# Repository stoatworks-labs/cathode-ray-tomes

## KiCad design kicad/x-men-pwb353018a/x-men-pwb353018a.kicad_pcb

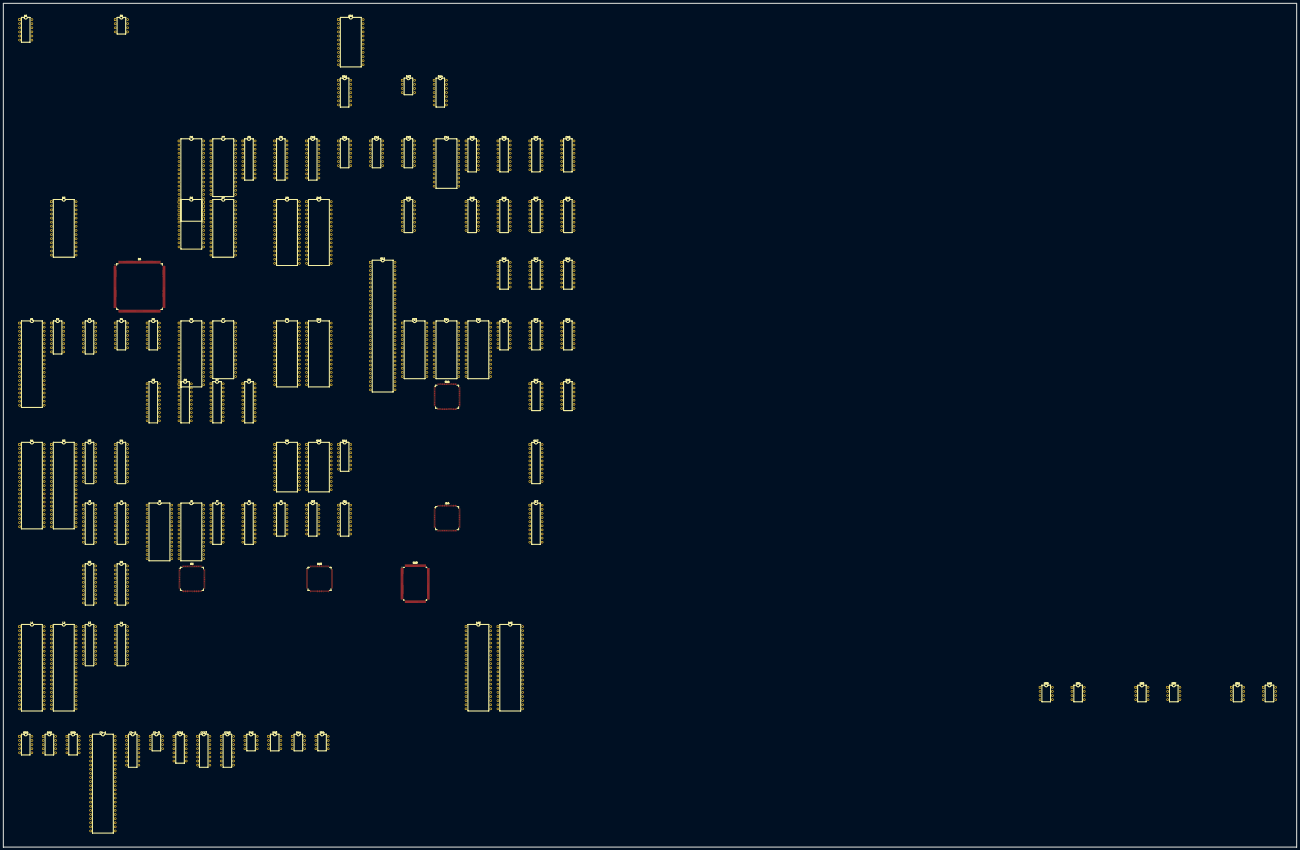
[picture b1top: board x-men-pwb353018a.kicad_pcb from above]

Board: 2 copper layers, 798.9 x 521.2 mm, 105 parts (0 on the bottom side), 659 nets, no tracks yet.

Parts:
A1: MB3722; DIP-12_W7.62mm
A4: LM358; DIP-8_W7.62mm
A11: 051550; DIP-24_W15.24mm
B11: 74LS07; DIP-14_W7.62mm
B13: ER5911; DIP-8_W7.62mm
B14: 74LS32; DIP-14_W7.62mm
BB9: 052535; DIP-10_W7.62mm
BG9: 052535; DIP-10_W7.62mm
BR9: 052535; DIP-10_W7.62mm
C4-1: 054321; DIP-48_W15.24mm
C4-2: AD1868R; DIP-16_W7.62mm
C4-3: MC33202; DIP-8_W7.62mm
C6: Z80CPU; DIP-40_W15.24mm
C7: MB8464A-10W-15W; DIP-28_W15.24mm
C8: PAL16L8; DIP-20_W7.62mm
C9, C10: 74LS273; DIP-20_W7.62mm
C11, C12: 74LS07; DIP-14_W7.62mm
C13: 74LS32; DIP-14_W7.62mm
C14: GAL22V10; DIP-24_W15.24mm
C15, C17, C18: 74LS257; DIP-16_W7.62mm
C16: 74LS367; DIP-16_W7.62mm
CC11: 74LS07; DIP-14_W7.62mm
CC13: 74LS174; DIP-16_W7.62mm
CC15: 74LS257; DIP-16_W7.62mm
D2: HM62256BLP; DIP-28_W15.24mm
D6: YM2151; DIP-24_W15.24mm
D7: MB8464A-10W-15W; DIP-28_W15.24mm
D9, D10: 27C020; DIP-32_W15.24mm
D13: 74LS161; DIP-16_W7.62mm
D15: 74LS139; DIP-16_W7.62mm
D16, D18: 74LS367; DIP-16_W7.62mm
D17: 74LS175; DIP-16_W7.62mm
E4: 054539; PQFP-160_28x28mm_P0.65mm
E12: 68000D; DIP-64_W15.24mm
E16: 74LS00; DIP-14_W7.62mm
E17: 74LS04; DIP-14_W7.62mm
E18: 74LS74; DIP-14_W7.62mm
F1: HN624116P; DIP-42_W15.24mm
F2: 74LS157; DIP-16_W7.62mm
F3: 74LS174; DIP-16_W7.62mm
F4, F17, F18: 74LS32; DIP-14_W7.62mm
F5: 74LS74; DIP-14_W7.62mm
F6, F9, F10: 27C020; DIP-32_W15.24mm
F7: MB8464A-10W-15W; DIP-28_W15.24mm
F13, F14, F15: MB8464A-80-10-15/L-LL; DIP-28_W15.24mm
F16: 74LS08; DIP-14_W7.62mm
G5, G6, G7, G8: 74LS245; DIP-20_W7.62mm
G14: 052109; TQFP-120_14x14mm_P0.4mm
G17: 74LS164; DIP-14_W7.62mm
G18: 74LS74; DIP-14_W7.62mm
H1, H2: 065A08; DIP-42_W15.24mm
H3, H4: 74LS374; DIP-20_W7.62mm
H9, H10: HM6116P-3; DIP-24_W15.24mm
H11: 74LS04; DIP-14_W7.62mm
H17: 74LS373; DIP-20_W7.62mm
J3, J4: 74LS374; DIP-20_W7.62mm
J5, J6: MB8464A-80-10-15/L-LL; DIP-28_W15.24mm
J7, J8: 74LS245; DIP-20_W7.62mm
J9, J10, J11: 74LS157; DIP-16_W7.62mm
J14: 051962; TQFP-120_14x14mm_P0.4mm
J17: 74LS373; DIP-20_W7.62mm
K3, K4: 74LS374; DIP-20_W7.62mm
K6: 053246; TQFP-120_14x14mm_P0.4mm
K10: 053247; TQFP-120_14x14mm_P0.4mm
K13: 053251; PQFP-100_14x20mm_P0.65mm
L1, L2, L15, L16: 065A08; DIP-42_W15.24mm
L3, L4: 74LS374; DIP-20_W7.62mm
S33, S34, S36, S37, S39, S40, S42, S43, S44, S54: KONAMI_005273; DIP-8_W7.62mm

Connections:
/+12V: A1.10, A11.19
/ACOL0: J14.46, K13.4
/ACOL1: J14.47, K13.5
/ACOL2: J14.48, K13.6
/ACOL3: J14.49, K13.7
/APAL0: J14.56, K13.8
/APAL1: J14.57, K13.9
/APAL2: J14.50, K13.10
/APAL3: J14.51, K13.20
/APAL4: J14.52, K13.21
/BCOL0: J14.30, K13.47
/BCOL1: J14.32, K13.48
/BCOL2: J14.33, K13.49
/BCOL3: J14.34, K13.50
/BPAL0: J14.35, K13.51
/BPAL1: J14.36, K13.52
/BPAL2: J14.37, K13.54
/BPAL3: J14.41, K13.55
/BPAL4: J14.42, K13.56
/BUSY: E4.11, F16.9
/COIN_CNT_1: A11.22, A11.23
/COIN_CNT_2: A11.20, A11.21
/CRAM~CS: C14.20, G7.19, G8.19, J9.1, J9.14, J10.1, J11.1
/CR~CS: D15.7, K10.9
/FCOL0: J14.59, K13.57
/FCOL1: J14.60, K13.58
/FCOL2: J14.62, K13.59
/FCOL3: J14.63, K13.60
/FPAL0: J14.64, K13.61
/FPAL1: J14.65, K13.62
/FPAL2: J14.66, K13.63
/FPAL3: J14.67, K13.64
/INTDMAEN: CC13.15, E18.10
/MAIN_A0: G6.3, G14.66, J14.88, K6.7, K10.7, K13.85
/MAIN_A1: C4-1.35, D7.10, D9.12, D10.12, E12.29, E17.1, F7.10, F9.12, F10.12, G6.4, G14.67, J11.2, J14.89, K6.6, K10.6, K13.84
/MAIN_A2: C4-1.34, D7.9, D9.11, D10.11, D15.2, E12.30, F7.9, F9.11, F10.11, G6.5, G14.68, J11.5, K13.83
/MAIN_A3: C4-1.33, D7.8, D9.10, D10.10, D15.3, E12.31, F7.8, F9.10, F10.10, G6.6, G14.69, J11.11, K13.82
/MAIN_A4: C4-1.32, D7.7, D9.9, D10.9, E12.32, F7.7, F9.9, F10.9, G6.7, G14.116, J11.14
/MAIN_A5: D7.6, D9.8, D10.8, D15.14, E12.33, F7.6, F9.8, F10.8, G6.8, G14.115, J10.2
/MAIN_A6: D7.5, D9.7, D10.7, D15.13, E12.34, F7.5, F9.7, F10.7, G6.9, G14.114, J10.5
/MAIN_A7: D7.4, D9.6, D10.6, E12.35, F7.4, F9.6, F10.6, G5.2, G14.113, J10.11
/MAIN_A8: D7.3, D9.5, D10.5, E12.36, F7.3, F9.5, F10.5, G5.3, G14.112, J10.14
/MAIN_A9: D7.25, D9.27, D10.27, E12.37, F7.25, F9.27, F10.27, G5.4, G14.111, J9.2
/MAIN_A10: D7.24, D9.26, D10.26, E12.38, F7.24, F9.26, F10.26, G5.5, G14.110, J9.5
/MAIN_A11: D7.21, D9.23, D10.23, E12.39, F7.21, F9.23, F10.23, G5.6, G14.109, J9.11
/MAIN_A12: D7.23, D9.25, D10.25, E12.40, F7.23, F9.25, F10.25, G6.2, G14.80
/MAIN_A13: C14.13, D7.2, D9.4, D10.4, E12.41, F7.2, F9.4, F10.4, G14.81
/MAIN_A14: C14.11, D9.28, D10.28, E12.42, F9.28, F10.28, G14.82
/MAIN_A15: C14.10, D9.29, D10.29, E12.43, F9.29, F10.29, G14.83
/MAIN_A16: C14.9, D9.3, D10.3, E12.44, F9.3, F10.3
/MAIN_A17: C14.8, D9.2, D10.2, E12.45, F9.2, F10.2
/MAIN_A18: C14.7, D9.30, D10.30, E12.46, F9.30, F10.30
/MAIN_A19: C13.13, C14.6, E12.47, E17.3
/MAIN_A20: C14.5, E12.48
/MAIN_A23: C14.4, E12.52, E16.13
/MAIN_D0: C4-1.44, CC13.3, CC15.4, D16.3, E12.5, F7.11, F9.13, F10.13, G7.2, G14.56, J7.2, J14.79, K10.30, K13.80
/MAIN_D1: C4-1.43, CC13.4, CC15.7, D16.5, E12.4, F7.12, F9.14, F10.14, G7.3, G14.57, J7.3, J14.80, K10.29, K13.79
/MAIN_D2: C4-1.42, CC13.6, CC15.9, D16.7, E12.3, F7.13, F9.15, F10.15, G7.4, G14.58, J7.4, J14.81, K10.28, K13.77
/MAIN_D3: C4-1.41, CC13.11, CC15.12, D16.9, E12.2, F7.15, F9.17, F10.17, G7.5, G14.59, J7.5, J14.82, K10.27, K13.76
/MAIN_D4: C4-1.40, C15.4, CC13.13, E12.1, F7.16, F9.18, F10.18, G7.6, G14.60, J7.6, J14.83, K10.26, K13.75
/MAIN_D5: C4-1.39, C15.7, CC13.14, E12.64, F7.17, F9.19, F10.19, G7.7, G14.62, J7.7, J14.84, K10.25, K13.74
/MAIN_D6: C4-1.38, C15.9, D16.11, E12.63, F7.18, F9.20, F10.20, G7.8, G14.63, J7.8, K10.24
/MAIN_D7: C4-1.37, C15.12, D16.13, E12.62, F7.19, F9.21, F10.21, G7.9, G14.64, J7.9, J14.86, K10.23
/MAIN_D8: C16.3, C18.4, D7.11, D9.13, D10.13, D17.4, E12.61, G8.2, J8.2, K10.22
/MAIN_D9: C16.5, C18.7, D7.12, D9.14, D10.14, D17.5, E12.60, G8.3, J8.3, K10.20
/MAIN_D10: C16.7, C18.9, D7.13, D9.15, D10.15, D17.12, E12.59, G8.4, J8.4, K10.19
/MAIN_D11: C16.9, C18.12, D7.15, D9.17, D10.17, D17.13, E12.58, G8.5, J8.5, K10.18
/MAIN_D12: C17.4, D7.16, D9.18, D10.18, E12.57, G8.6, J8.6, K10.17
/MAIN_D13: C17.7, D7.17, D9.19, D10.19, E12.56, G8.7, J8.7, K10.15
/MAIN_D14: C16.11, C17.9, D7.18, D9.20, D10.20, E12.55, G8.8, J8.8, K10.14
/MAIN_D15: C16.13, C17.12, D7.19, D9.21, D10.21, E12.54, G8.9, J8.9, K10.13
/MAIN~IRQ: F16.2, F17.2, G14.87
/MCLK: D13.14, E12.15
/MCO~WRH: F18.3, H10.21
/MCO~WRL: F18.6, H9.21
/MUTE: C12.1, D17.14
/M~RD: B14.9, C13.5, E17.8, G5.7, G7.1, G8.1, G14.85, J7.1, J8.1, J14.87
/OBJCLK6: C9.11, C10.11, E17.13, H11.11, J14.78, K6.12, K10.12
/OBJCLK12: H11.3, J14.95, K6.10, K10.10
/OBJDMA: F17.9, G5.19, G6.19, H11.1, K6.116
/OBJROMA0: H1.10, H2.10, K6.68, L1.10, L2.10
/OBJROMA1: H1.9, H2.9, K6.69, L1.9, L2.9
/OBJROMA2: H1.8, H2.8, K6.70, L1.8, L2.8
/OBJROMA3: H1.7, H2.7, K6.72, L1.7, L2.7
/OBJROMA4: H1.6, H2.6, K6.73, L1.6, L2.6
/OBJROMA5: H1.5, H2.5, K6.74, L1.5, L2.5
/OBJROMA6: H1.4, H2.4, K6.75, L1.4, L2.4
/OBJROMA7: H1.3, H2.3, K6.77, L1.3, L2.3
/OBJROMA8: H1.41, H2.41, K6.78, L1.41, L2.41
/OBJROMA9: H1.40, H2.40, K6.79, L1.40, L2.40
/OBJROMA10: H1.39, H2.39, K6.80, L1.39, L2.39
/OBJROMA11: H1.38, H2.38, K6.82, L1.38, L2.38
/OBJROMA12: H1.37, H2.37, K6.83, L1.37, L2.37
/OBJROMA13: H1.36, H2.36, K6.84, L1.36, L2.36
/OBJROMA14: H1.35, H2.35, K6.85, L1.35, L2.35
/OBJROMA15: H1.34, H2.34, K6.86, L1.34, L2.34
/OBJROMA16: H1.33, H2.33, K6.87, L1.33, L2.33
/OBJROMA17: H1.2, H2.2, K6.88, L1.2, L2.2
/OBJROMA18: H1.1, H2.1, K6.89, L1.1, L2.1
/OBJROMA19: H1.42, H2.42, K6.90, L1.42, L2.42
/OBJ~CS: C14.18, F16.13
/OBJ~REG: D15.11, F16.12, K6.2, K10.2
/OCHARA: D17.3, K6.9
/OCOL0: K10.32, K13.30
/OCOL1: K10.33, K13.31
/OCOL2: K10.34, K13.32
/OCOL3: K10.35, K13.33
/OCOL4: K10.36, K13.34
/OCOL5: K10.37, K13.35
/OCOL6: K10.38, K13.36
/OCOL7: K10.39, K13.37
/OCOL8: K10.40, K13.38
/OPRI0: K10.42, K13.23
/OPRI1: K10.43, K13.24
/OPRI2: K10.44, K13.25
/OPRI3: K10.45, K13.27
/OPRI4: K10.47, K13.29
/ORAM~WEH: F4.6, J5.27
/ORAM~WEL: F4.8, J6.27
/PAIR~CS: C4-1.36, D15.10
/PAS: E16.12, E17.10, F5.11
/PCM0: C4-1.1, E4.34
/PCM1: C4-1.2, E4.26
/PCM2: C4-1.3, E4.27
/PCU~CS: D15.9, K13.81
/R/~W: B14.2, B14.13, C14.2, E12.9, E17.9
/SCR_PQ: E18.3, F18.13, G14.89
/SCR~CLK: G14.65, G18.3, H11.6, J14.90
/SHD0: K10.48, K13.95
/SHD1: K10.49, K13.96
/SIC_CLK: C4-1.7, C4-2.4, E4.28
/SND_A0: C4-1.21, C6.30, C7.10, D6.4, E4.52, F6.12
/SND_A1: C4-1.22, C6.31, C7.9, E4.51, F6.11
/SND_A2: C6.32, C7.8, E4.49, F6.10
/SND_A3: C6.33, C7.7, E4.48, F6.9
/SND_A4: C6.34, C7.6, E4.47, F6.8
/SND_A5: C6.35, C7.5, E4.46, F6.7
/SND_A6: C6.36, C7.4, E4.45, F6.6
/SND_A7: C6.37, C7.3, E4.44, F6.5
/SND_A8: C6.38, C7.25, F6.27
/SND_A9: C6.39, C7.24, E4.42, F6.26
/SND_A10: C6.40, C7.21, C8.11, F6.23
/SND_A11: C6.1, C7.23, C8.9, F6.25
/SND_A12: C6.2, C7.2, C8.8, F6.4
/SND_A13: C6.3, C8.7, F6.28
/SND_A14: C6.4, C8.6
/SND_A15: C6.5, C8.5, F2.1
/SND_D0: C4-1.12, C6.14, C7.11, D6.10, E4.9, F3.3, F6.13
/SND_D1: C4-1.13, C6.15, C7.12, D6.12, E4.8, F3.4, F6.14
/SND_D2: C4-1.14, C6.12, C7.13, D6.13, E4.7, F3.6, F6.15
/SND_D3: C4-1.15, C6.8, C7.15, D6.14, E4.6, F3.11, F6.17
/SND_D4: C4-1.16, C6.7, C7.16, D6.15, E4.5, F3.13, F6.18
/SND_D5: C4-1.17, C6.9, C7.17, D6.16, E4.4, F3.14, F6.19
/SND_D6: C4-1.18, C6.10, C7.18, D6.17, E4.3, F6.20
/SND_D7: C4-1.19, C6.13, C7.19, D6.18, E4.2, F6.21
/SND~PAL8: C4-1.24, C8.12
/SYS~RES: G14.55, G18.5, J14.92
/S~CLK: C4-1.5, C6.6, D13.13
/S~INT: C4-1.8, C6.16
/S~IORQ: C4-1.29, C6.20
/S~RD: C4-1.25, C6.21, C7.22, C8.2, D6.6, E4.67
/S~RST: C4-1.4, C6.26, D6.3, E4.71, F3.1
/S~WAIT: C6.24, F16.8
/S~WR: C4-1.26, C6.22, C7.27, D6.5, E4.68
/VSYNC: H11.8, K6.119
/V~CHARA: D17.7, G14.97, J14.96
/XOBJROMD0: K3.3, L1.14
/XOBJROMD1: K3.4, L1.16
/XOBJROMD2: K3.7, L1.18
/XOBJROMD3: K3.8, L1.20
/XOBJROMD4: K3.13, L1.23
/XOBJROMD5: K3.14, L1.25
/XOBJROMD6: K3.17, L1.27
/XOBJROMD7: K3.18, L1.29
/XOBJROMD8: L1.15, L3.3
/XOBJROMD9: L1.17, L3.4
/XOBJROMD10: L1.19, L3.7
/XOBJROMD11: L1.21, L3.8
/XOBJROMD12: L1.24, L3.13
/XOBJROMD13: L1.26, L3.14
/XOBJROMD14: L1.28, L3.17
/XOBJROMD15: L1.30, L3.18
/XOBJROMD16: H1.14, H3.3
/XOBJROMD17: H1.16, H3.4
/XOBJROMD18: H1.18, H3.7
/XOBJROMD19: H1.20, H3.8
/XOBJROMD20: H1.23, H3.13
/XOBJROMD21: H1.25, H3.14
/XOBJROMD22: H1.27, H3.17
/XOBJROMD23: H1.29, H3.18
/XOBJROMD24: H1.15, J3.3
/XOBJROMD25: H1.17, J3.4
/XOBJROMD26: H1.19, J3.7
/XOBJROMD27: H1.21, J3.8
/XOBJROMD28: H1.24, J3.13
/XOBJROMD29: H1.26, J3.14
/XOBJROMD30: H1.28, J3.17
/XOBJROMD31: H1.30, J3.18
/YOBJROMD0: K4.3, L2.14
/YOBJROMD1: K4.4, L2.16
/YOBJROMD2: K4.7, L2.18
/YOBJROMD3: K4.8, L2.20
/YOBJROMD4: K4.13, L2.23
/YOBJROMD5: K4.14, L2.25
/YOBJROMD6: K4.17, L2.27
/YOBJROMD7: K4.18, L2.29
/YOBJROMD8: L2.15, L4.3
/YOBJROMD9: L2.17, L4.4
/YOBJROMD10: L2.19, L4.7
/YOBJROMD11: L2.21, L4.8
/YOBJROMD12: L2.24, L4.13
/YOBJROMD13: L2.26, L4.14
/YOBJROMD14: L2.28, L4.17
/YOBJROMD15: L2.30, L4.18
/YOBJROMD16: H2.14, H4.3
/YOBJROMD17: H2.16, H4.4
/YOBJROMD18: H2.18, H4.7
/YOBJROMD19: H2.20, H4.8
/YOBJROMD20: H2.23, H4.13
/YOBJROMD21: H2.25, H4.14
/YOBJROMD22: H2.27, H4.17
/YOBJROMD23: H2.29, H4.18
/YOBJROMD24: H2.15, J4.3
/YOBJROMD25: H2.17, J4.4
/YOBJROMD26: H2.19, J4.7
/YOBJROMD27: H2.21, J4.8
/YOBJROMD28: H2.24, J4.13
/YOBJROMD29: H2.26, J4.14
/YOBJROMD30: H2.28, J4.17
/YOBJROMD31: H2.30, J4.18
/colmix/COL0: J11.3, K13.19
/colmix/COL1: J11.6, K13.18
/colmix/COL2: J11.10, K13.17
/colmix/COL3: J11.13, K13.16
/colmix/COL4: J10.3, K13.14
/colmix/COL5: J10.6, K13.13
/colmix/COL6: J10.10, K13.12
/colmix/COL7: J10.13, K13.11
/colmix/COL8: J9.3, K13.93
/colmix/COL9: J9.6, K13.92
/colmix/COL10: J9.10, K13.91
/colmix/MCOL0: H9.8, H10.8, J11.4
/colmix/MCOL1: H9.7, H10.7, J11.7
/colmix/MCOL2: H9.6, H10.6, J11.9
/colmix/MCOL3: H9.5, H10.5, J11.12
/colmix/MCOL4: H9.4, H10.4, J10.4
/colmix/MCOL5: H9.3, H10.3, J10.7
/colmix/MCOL6: H9.2, H10.2, J10.9
/colmix/MCOL7: H9.1, H10.1, J10.12
/colmix/MCOL8: H9.23, H10.23, J9.4
/colmix/MCOL9: H9.22, H10.22, J9.7
/colmix/MCOL10: H9.19, H10.19, J9.9
/colmix/RGB0: C10.3, G7.18, H9.9
/colmix/RGB1: C10.4, G7.17, H9.10
/colmix/RGB2: C10.7, G7.16, H9.11
/colmix/RGB3: C10.8, G7.15, H9.13
/colmix/RGB4: C10.13, G7.14, H9.14
/colmix/RGB5: C10.14, G7.13, H9.15
/colmix/RGB6: C10.17, G7.12, H9.16
/colmix/RGB7: C10.18, G7.11, H9.17
/colmix/RGB8: C9.3, G8.18, H10.9
/colmix/RGB9: C9.4, G8.17, H10.10
/colmix/RGB10: C9.7, G8.16, H10.11
/colmix/RGB11: C9.8, G8.15, H10.13
/colmix/RGB12: C9.13, G8.14, H10.14
/colmix/RGB13: C9.14, G8.13, H10.15
/colmix/RGB14: C9.17, G8.12, H10.16
/colmix/RGB15: G8.11, H10.17
/colmix/SHAD: F18.8, H11.13
/colmix/rgb/B10: C9.6, CC11.9
/colmix/rgb/B11: B11.11, C9.9
/colmix/rgb/B12: B11.9, C9.12
/colmix/rgb/B13: C9.15, C12.11
/colmix/rgb/B14: C9.16, C12.9
/colmix/rgb/G5: C10.15, C11.9
/colmix/rgb/G6: C10.16, CC11.11
/colmix/rgb/G7: C10.19, CC11.13
/colmix/rgb/G8: C9.2, C11.3
/colmix/rgb/G9: C9.5, C11.1
/colmix/rgb/R0: C10.2, C11.13
/colmix/rgb/R1: C10.5, C11.5
/colmix/rgb/R2: C10.6, C11.11
/colmix/rgb/R3: B11.1, C10.9
/colmix/rgb/R4: B11.13, C10.12
/colmix/rgb/~SHADOW: B11.5, C9.19, CC11.3, CC11.5
/colmix/~COLOE: H9.20, H10.20, J9.12
/io_cabinet/AFE: A11.1, F5.8
/io_cabinet/CAB0: D16.2, S54.1
/io_cabinet/CAB1: D16.4, S54.3
/io_cabinet/CAB2: D16.6, S54.5
/io_cabinet/CAB3: D16.10, S54.7
/io_cabinet/CAB6: B13.4, D16.12
/io_cabinet/CAB7: B13.7, D16.14
/io_cabinet/CAB8: C16.2, S44.1
/io_cabinet/CAB9: C16.4, S44.3
/io_cabinet/CAB10: C16.6, S44.5
/io_cabinet/CAB11: C16.10, S44.7
/io_cabinet/JOYSTICK: C15.15, C17.15, C18.15, CC15.15, D15.4
/io_cabinet/OTHER: C16.1, C16.15, D15.5, D16.1, D16.15
/io_cabinet/R1P_BTN_1: C15.2, S39.1
/io_cabinet/R1P_BTN_2: C15.5, S39.5
/io_cabinet/R1P_BTN_3: C15.11, S40.1
/io_cabinet/R1P_DOWN: CC15.5, S42.5
/io_cabinet/R1P_LEFT: CC15.11, S43.1
/io_cabinet/R1P_RIGHT: CC15.14, S43.5
/io_cabinet/R1P_UP: CC15.2, S42.1
/io_cabinet/R2P_BTN_1: C15.3, S39.3
/io_cabinet/R2P_BTN_2: C15.6, S39.7
/io_cabinet/R2P_BTN_3: C15.10, S40.3
/io_cabinet/R2P_DOWN: CC15.6, S42.7
/io_cabinet/R2P_LEFT: CC15.10, S43.3
/io_cabinet/R2P_RIGHT: CC15.13, S43.7
/io_cabinet/R2P_UP: CC15.3, S42.3
/io_cabinet/R3P_BTN_1: C17.2, S33.1
/io_cabinet/R3P_BTN_2: C17.5, S33.5
/io_cabinet/R3P_BTN_3: C17.11, S34.1
/io_cabinet/R3P_DOWN: C18.5, S36.5
/io_cabinet/R3P_LEFT: C18.11, S37.1
/io_cabinet/R3P_RIGHT: C18.14, S37.5
/io_cabinet/R3P_UP: C18.2, S36.1
/io_cabinet/R4P_BTN_1: C17.3, S33.3
/io_cabinet/R4P_BTN_2: C17.6, S33.7
/io_cabinet/R4P_BTN_3: C17.10, S34.3
/io_cabinet/R4P_DOWN: C18.6, S36.7
/io_cabinet/R4P_LEFT: C18.10, S37.3
/io_cabinet/R4P_RIGHT: C18.13, S37.7
/io_cabinet/R4P_UP: C18.3, S36.3
/io_cabinet/RCOIN_1: C15.14, S40.5
/io_cabinet/RCOIN_2: C15.13, S40.7
/io_cabinet/RCOIN_3: C17.14, S34.5
/io_cabinet/RCOIN_4: C17.13, S34.7
/io_cabinet/~MAIN_A1: C15.1, C17.1, C18.1, CC15.1, E17.2
/main/CO~WR: C14.21, F18.1, F18.5
/main/INTDMA: E16.5, E18.9, F16.1
/main/MRAM~WEH: D7.27, F4.3
/main/MRAM~WEL: F4.11, F7.27
/main/PROMOE1: C13.11, D10.24, F10.24
/main/PROM~OE2: C13.8, D9.24, F9.24
/main/VSC: C14.3, F18.11
/main/~AS: C13.2, C14.1, E12.6, E17.11
/main/~OBWR: C14.19, F4.4, F4.10
/main/~PROG: C13.1, C14.14
/main/~VRAM: C14.17, E18.2
/main/~WKCS: B14.12, C13.4, C14.15
/objects/CLKOBJ': H3.11, H4.11, J3.11, J4.11, K3.11, K4.11, K6.66, L3.11, L4.11
/objects/EA1: G6.17, J5.9, J6.9, K6.112
/objects/EA2: G6.16, J5.8, J6.8, K6.110
/objects/EA3: G6.15, J5.7, J6.7, K6.109
/objects/EA4: G6.14, J5.6, J6.6, K6.108
/objects/EA5: G6.18, J5.10, J6.10, K6.107
/objects/EN0: G6.13, J5.5, J6.5, K6.105
/objects/EN1: G6.12, J5.4, J6.4, K6.104
/objects/EN2: G6.11, J5.3, J6.3, K6.103
/objects/EN3: G5.18, J5.25, J6.25, K6.102
/objects/EN4: G5.17, J5.24, J6.24, K6.100
/objects/EN5: G5.16, J5.21, J6.21, K6.99
/objects/EN6: G5.15, J5.23, J6.23, K6.98
/objects/EN7: G5.14, J5.2, J6.2, K6.97
/objects/G2D0: K6.32, K10.119
/objects/G2D1: K6.33, K10.118
/objects/G2D2: K6.34, K10.117
/objects/G2D3: K6.35, K10.116
/objects/G2D4: K6.36, K10.115
/objects/G2D5: K6.37, K10.114
/objects/G2D6: K6.38, K10.113
/objects/G2D7: K6.39, K10.112
/objects/G2D8: K6.40, K10.110
/objects/G2D9: K6.42, K10.109
/objects/G2D10: K6.43, K10.108
/objects/G2D11: K6.44, K10.107
/objects/G2D12: K6.45, K10.105
/objects/G2D13: K6.47, K10.104
/objects/G2D14: K6.48, K10.103
/objects/G2D15: K6.49, K10.102
/objects/G2D16: K6.50, K10.100
/objects/G2D17: K6.52, K10.99
/objects/G2D18: K6.53, K10.98
/objects/G2D19: K6.54, K10.97
/objects/G2D20: K6.55, K10.96
/objects/G2D21: K6.56, K10.95
/objects/LUTD0: J6.11, J7.18, K6.30
/objects/LUTD1: J6.12, J7.17, K6.29
/objects/LUTD2: J6.13, J7.16, K6.28
/objects/LUTD3: J6.15, J7.15, K6.27
/objects/LUTD4: J6.16, J7.14, K6.26
/objects/LUTD5: J6.17, J7.13, K6.25
/objects/LUTD6: J6.18, J7.12, K6.24
/objects/LUTD7: J6.19, J7.11, K6.23
/objects/LUTD8: J5.11, J8.18, K6.22
/objects/LUTD9: J5.12, J8.17, K6.20
/objects/LUTD10: J5.13, J8.16, K6.19
/objects/LUTD11: J5.15, J8.15, K6.18
/objects/LUTD12: J5.16, J8.14, K6.17
/objects/LUTD13: J5.17, J8.13, K6.15
/objects/LUTD14: J5.18, J8.12, K6.14
/objects/LUTD15: J5.19, J8.11, K6.13
/objects/OBJROMD'0: H3.2, H4.2, K3.2, K4.2, K10.72
/objects/OBJROMD'1: H3.5, H4.5, K3.5, K4.5, K10.73
/objects/OBJROMD'2: H3.6, H4.6, K3.6, K4.6, K10.74
/objects/OBJROMD'3: H3.9, H4.9, K3.9, K4.9, K10.75
/objects/OBJROMD'4: H3.12, H4.12, K3.12, K4.12, K10.77
/objects/OBJROMD'5: H3.15, H4.15, K3.15, K4.15, K10.78
/objects/OBJROMD'6: H3.16, H4.16, K3.16, K4.16, K10.79
/objects/OBJROMD'7: H3.19, H4.19, K3.19, K4.19, K10.80
/objects/OBJROMD'8: J3.2, J4.2, K10.82, L3.2, L4.2
/objects/OBJROMD'9: J3.5, J4.5, K10.83, L3.5, L4.5
/objects/OBJROMD'10: J3.6, J4.6, K10.84, L3.6, L4.6
/objects/OBJROMD'11: J3.9, J4.9, K10.85, L3.9, L4.9
/objects/OBJROMD'12: J3.12, J4.12, K10.86, L3.12, L4.12
/objects/OBJROMD'13: J3.15, J4.15, K10.87, L3.15, L4.15
/objects/OBJROMD'14: J3.16, J4.16, K10.88, L3.16, L4.16
/objects/OBJROMD'15: J3.19, J4.19, K10.89, L3.19, L4.19
/objects/~CE: F17.8, J7.19, J8.19
/objects/~RD: G5.13, J5.22, J6.22, K6.114
/objects/~SET0: K3.1, K6.65, K10.90, L3.1
/objects/~SET1: H3.1, J3.1, K6.64, K10.92
/objects/~SET2: K4.1, K6.63, K10.93, L4.1
/objects/~SET3: H4.1, J4.1, K6.62, K10.94
/pcm/MUTEB: A1.3, C4-2.1, C4-2.9, C4-2.15
/pcm/~WAIT: C4-1.23, F16.10
/scroll/GFXROMA0: G14.35, J17.3
/scroll/GFXROMA1: G14.34, J17.4
/scroll/GFXROMA2: G14.33, J17.7
/scroll/GFXROMA3: G14.32, L15.7, L16.7
/scroll/GFXROMA4: G14.30, L15.6, L16.6
/scroll/GFXROMA5: G14.29, L15.5, L16.5
/scroll/GFXROMA6: G14.28, L15.4, L16.4
/scroll/GFXROMA7: G14.27, L15.3, L16.3
/scroll/GFXROMA8: G14.26, L15.41, L16.41
/scroll/GFXROMA9: G14.25, L15.40, L16.40
/scroll/GFXROMA10: G14.24, L15.39, L16.39
/scroll/GFXROMA11: G14.37, H17.3, J14.114
/scroll/GFXROMA12: G14.38, H17.4, J14.113
/scroll/GFXROMA13: G14.39, H17.7, J14.112
/scroll/GFXROMA14: G14.40, H17.8, J14.111
/scroll/GFXROMA15: G14.41, H17.13, J14.110
/scroll/GFXROMA16: G14.42, H17.14, J14.109
/scroll/GFXROMA17: G14.43, H17.17, J14.108
/scroll/GFXROMA18: G14.46, H17.18, J14.107
/scroll/GFXROMA'0: J17.2, L15.10, L16.10
/scroll/GFXROMA'1: J17.5, L15.9, L16.9
/scroll/GFXROMA'2: J17.6, L15.8, L16.8
/scroll/GFXROMA'11: H17.2, L15.38, L16.38
/scroll/GFXROMA'12: H17.5, L15.37, L16.37
/scroll/GFXROMA'13: H17.6, L15.36, L16.36
/scroll/GFXROMA'14: H17.9, L15.35, L16.35
/scroll/GFXROMA'15: H17.12, L15.34, L16.34
/scroll/GFXROMA'16: H17.15, L15.33, L16.33
/scroll/GFXROMA'17: H17.16, L15.2, L16.2
/scroll/GFXROMA'18: H17.19, L15.1, L16.1
/scroll/GFXROMD0: J14.29, L15.14
/scroll/GFXROMD1: J14.28, L15.16
/scroll/GFXROMD2: J14.27, L15.18
/scroll/GFXROMD3: J14.26, L15.20
/scroll/GFXROMD4: J14.25, L15.23
/scroll/GFXROMD5: J14.24, L15.25
/scroll/GFXROMD6: J14.23, L15.27
/scroll/GFXROMD7: J14.22, L15.29
/scroll/GFXROMD8: J14.21, L15.15
/scroll/GFXROMD9: J14.20, L15.17
/scroll/GFXROMD10: J14.19, L15.19
/scroll/GFXROMD11: J14.18, L15.21
/scroll/GFXROMD12: J14.17, L15.24
/scroll/GFXROMD13: J14.16, L15.26
/scroll/GFXROMD14: J14.13, L15.28
/scroll/GFXROMD15: J14.12, L15.30
/scroll/GFXROMD16: J14.11, L16.14
/scroll/GFXROMD17: J14.10, L16.16
/scroll/GFXROMD18: J14.9, L16.18
/scroll/GFXROMD19: J14.8, L16.20
/scroll/GFXROMD20: J14.7, L16.23
/scroll/GFXROMD21: J14.6, L16.25
/scroll/GFXROMD22: J14.5, L16.27
/scroll/GFXROMD23: J14.4, L16.29
/scroll/GFXROMD24: J14.3, L16.15
/scroll/GFXROMD25: J14.2, L16.17
/scroll/GFXROMD26: J14.120, L16.19
/scroll/GFXROMD27: J14.119, L16.21
/scroll/GFXROMD28: J14.118, L16.24
/scroll/GFXROMD29: J14.117, L16.26
/scroll/GFXROMD30: J14.116, L16.28
/scroll/GFXROMD31: J14.115, L16.30
/scroll/SCRAMA0: F13.10, F14.10, F15.10, G14.2
/scroll/SCRAMA1: F13.9, F14.9, F15.9, G14.120
/scroll/SCRAMA2: F13.8, F14.8, F15.8, G14.119
/scroll/SCRAMA3: F13.7, F14.7, F15.7, G14.118
/scroll/SCRAMA4: F13.6, F14.6, F15.6, G14.117
/scroll/SCRAMA5: F13.5, F14.5, F15.5, G14.70
/scroll/SCRAMA6: F13.4, F14.4, F15.4, G14.71
/scroll/SCRAMA7: F13.3, F14.3, F15.3, G14.72
/scroll/SCRAMA8: F13.25, F14.25, F15.25, G14.73
/scroll/SCRAMA9: F13.24, F14.24, F15.24, G14.76
/scroll/SCRAMA10: F13.21, F14.21, F15.21, G14.77
/scroll/SCRAMA11: F13.23, F14.23, F15.23, G14.78
/scroll/SCRAMA12: F13.2, F14.2, F15.2, G14.79
/scroll/VD0: F15.11, G14.20
/scroll/VD1: F15.12, G14.19
/scroll/VD2: F15.13, G14.18
/scroll/VD3: F15.15, G14.17
/scroll/VD4: F15.16, G14.16
/scroll/VD5: F15.17, G14.13
/scroll/VD6: F15.18, G14.12
/scroll/VD7: F15.19, G14.11
/scroll/VD8: F13.11, F14.11, G14.10
/scroll/VD9: F13.12, F14.12, G14.9
/scroll/VD10: F13.13, F14.13, G14.8
/scroll/VD11: F13.15, F14.15, G14.7
/scroll/VD12: F13.16, F14.16, G14.6
/scroll/VD13: F13.17, F14.17, G14.5
/scroll/VD14: F13.18, F14.18, G14.4
/scroll/VD15: F13.19, F14.19, G14.3
/scroll/VDE: G14.36, G18.12, J17.11
/scroll/ZA1H: G14.50, J14.101
/scroll/ZA2H: G14.51, J14.100
/scroll/ZA4H: G14.52, J14.99
/scroll/ZB1H: G14.47, J14.106
/scroll/ZB2H: G14.48, J14.103
/scroll/ZB4H: G14.49, J14.102
/scroll/~BE: G14.53, J14.98
/scroll/~CSYNC: D18.10, J14.76
/scroll/~RCS0: F13.20, G14.92
/scroll/~RCS1: F14.20, G14.93
/scroll/~ROE0: F13.22, G14.94
/scroll/~ROE1: F14.22, G14.95
/scroll/~ROE2: F15.22, G14.96
/scroll/~RWE0: F13.27, G14.106
/scroll/~RWE1: F14.27, G14.107
/scroll/~RWE2: F15.27, G14.108
/sound/AUX1: D6.21, E4.39
/sound/GND: C8.10, D2.14
/sound/RAMR~W: D2.27, E4.107
/sound/RAM~CE: D2.20, E4.109
/sound/RAM~OE: D2.22, E4.108
/sound/ROM~CE: E4.133, F1.11
/sound/ROM~OE: E4.131, F1.13
/sound/R_A0: D2.10, E4.132, F1.30
/sound/R_A1: D2.9, E4.135, F1.10
/sound/R_A2: D2.8, E4.137, F1.9
/sound/R_A3: D2.7, E4.141, F1.8
/sound/R_A4: D2.6, E4.143, F1.7
/sound/R_A5: D2.5, E4.146, F1.6
/sound/R_A6: D2.4, E4.148, F1.5
/sound/R_A7: D2.3, E4.151, F1.4
/sound/R_A8: D2.25, E4.153, F1.3
/sound/R_A9: D2.24, E4.157, F1.41
/sound/R_A10: D2.21, E4.154, F1.40
/sound/R_A11: D2.23, E4.152, F1.39
/sound/R_A12: D2.2, E4.149, F1.38
/sound/R_A13: D2.26, E4.147, F1.37
/sound/R_A14: E4.144, F1.36
/sound/R_A15: E4.142, F1.35
/sound/R_A16: D2.1, E4.138, F1.34
/sound/R_A17: E4.136, F1.33
/sound/R_A18: E4.156, F1.2
/sound/R_A19: E4.158, F1.1
/sound/R_A20: E4.159, F1.42
/sound/R_D0: D2.11, E4.128, F1.14
/sound/R_D1: D2.12, E4.126, F1.16
/sound/R_D2: D2.13, E4.124, F1.18
/sound/R_D3: D2.15, E4.122, F1.20
/sound/R_D4: D2.16, E4.123, F1.23
/sound/R_D5: D2.17, E4.125, F1.25
/sound/R_D6: D2.18, E4.127, F1.27
/sound/R_D7: D2.19, E4.129, F1.29
/sound/SBANK0: F2.3, F3.2
/sound/SBANK1: F2.6, F3.5
/sound/SBANK2: F2.10, F3.7
/sound/SBANK3: F2.13, F3.10
/sound/SH1: D6.20, E4.37
/sound/SH2: D6.19, E4.36
/sound/SO~CLK: D6.23, E4.38
/sound/S~M1: C6.27, C8.1
/sound/S~MREQ: C6.19, C8.4
/sound/S~RFSH: C6.28, C8.3
/sound/~FM: C8.16, D6.7
/sound/~IRQ: D6.2, E16.1
/sound/~NMI_CLR: F3.12, F5.4
/sound/~NMI: C6.17, F5.5
/sound/~PCM: C8.17, E4.69
/sound/~SBANK_WR: C8.14, F3.9
/sound/~SRAM: C7.20, C8.18
/sound/~SROM: C8.19, F6.24
/sound/ØM: D6.24, D13.12
/~HBLANK: G17.2, J14.70
/~HSYNC: J14.73, K6.8, K10.8
/~IO1: C14.23, D15.15
/~IO2: B14.1, B14.10, C14.22
/~LDS: B14.4, E12.8, E17.5, F4.9, F4.12, F18.4, K6.4, K10.4
/~RESET: C12.3, C12.5, CC13.1, D17.1, G14.98, G17.9, K6.3, K10.3
/~SDON: C4-1.30, D17.10
/~SLATCHES: C4-1.20, C8.15
/~UDS: E12.7, F4.1, F4.5, F17.13, F18.2, K6.5, K10.5
/~VBLANK: G17.1, J14.69
/~VCS: E18.5, F18.12, G14.54, G14.84, J14.97
unnamed: A4.3, A4.5
unnamed: A11.15, CC13.2
unnamed: A11.16, CC13.5
unnamed: A11.10, G18.1, G18.2
unnamed: B13.2, CC13.10
unnamed: B13.1, CC13.12
unnamed: B13.3, CC13.7
unnamed: B14.11, F4.2, F4.13
unnamed: B11.4, BB9.7
unnamed: BB9.6, CC11.8
unnamed: B11.10, BB9.5
unnamed: B11.8, BB9.4
unnamed: BB9.3, C12.10
unnamed: BB9.2, C12.8
unnamed: BG9.7, C12.12
unnamed: BG9.6, C11.8
unnamed: BG9.5, CC11.10
unnamed: BG9.4, CC11.12
unnamed: BG9.3, C11.4
unnamed: BG9.2, C11.2
unnamed: BR9.7, CC11.2
unnamed: BR9.6, C11.12
unnamed: BR9.5, C11.6
unnamed: BR9.4, C11.10
unnamed: B11.2, BR9.3
unnamed: B11.12, BR9.2
unnamed: C4-1.9, C4-2.3
unnamed: C4-1.11, C4-2.5
unnamed: C4-1.10, C4-2.2, C4-2.6
unnamed: C9.18, H11.12
unnamed: C13.9, E17.4
unnamed: C13.3, C13.10, C13.12
unnamed: B14.6, CC13.9
unnamed: C13.6, D7.22, F7.22
unnamed: B14.8, D15.1
unnamed: B14.5, D15.12, F17.12
unnamed: D17.9, F17.11
unnamed: E4.20, E4.40, E4.56, E4.60, E4.73, E4.80, E4.100, E4.120, E4.140, E4.160
unnamed: C14.16, E12.10
unnamed: C12.6, E12.17
unnamed: E12.25, F16.3
unnamed: E12.24, E16.9, F17.3
unnamed: E12.23, E16.8
unnamed: C12.4, E12.18
unnamed: E12.21, E16.11
unnamed: E16.6, E16.10, F17.1
unnamed: E17.6, E18.4
unnamed: E18.11, H11.2
unnamed: F2.4, F6.29
unnamed: F2.7, F6.3
unnamed: F2.9, F6.2
unnamed: F2.12, F6.30
unnamed: E16.3, F5.3
unnamed: B14.3, F5.10
unnamed: F16.11, F17.10
unnamed: E17.12, G17.8
unnamed: B11.3, C12.13, CC11.1, G17.11
unnamed: G18.11, H11.4
unnamed: G18.9, H17.11
unnamed: H11.9, J14.72
unnamed: H11.10, K13.41
unnamed: F18.10, K13.87
unnamed: F18.9, K13.86
VCC: A4.8, A11.9, B11.14, B13.8, B14.14, BB9.1, BG9.1, BR9.1, C4-1.27, C4-3.8, C6.11, C7.26, C7.28, C8.20, C9.1, C10.1, C11.14, C12.14, C13.14, C14.24, C16.16, CC11.14, D2.28, D6.22, D7.26, D7.28, D9.1, D9.31, D9.32, D10.1, D10.31, D10.32, D13.1, D13.7, D13.9, D13.10, D15.16, D16.16, D18.16, E12.12, E12.13, E12.14, E12.22, E12.49, E16.2, E16.4, E16.14, E17.14, E18.1, E18.13, E18.14, F1.22, F4.14, F5.1, F5.13, F5.14, F6.1, F6.31, F6.32, F7.26, F7.28, F9.1, F9.31, F9.32, F10.1, F10.31, F10.32, F13.26, F13.28, F14.26, F14.28, F15.26, F15.28, F16.14, F17.14, F18.14, G5.1, G6.1, G14.14, G14.44, G14.74, G14.104, G17.14, G18.4, G18.10, G18.13, G18.14, H1.22, H1.32, H2.22, H2.32, H9.24, H10.24, H11.14, H17.20, J5.26, J5.28, J6.26, J6.28, J14.14, J14.44, J14.74, J14.104, J17.20, K6.16, K6.46, K6.59, K6.60, K6.76, K6.106, K6.120, K10.16, K10.46, K10.60, K10.70, K10.76, K10.106, K10.120, K13.1, K13.2, K13.3, K13.28, K13.39, K13.42, K13.43, K13.44, K13.45, K13.46, K13.53, K13.66, K13.78, K13.97, K13.98, K13.99, K13.100, L1.22, L1.32, L2.22, L2.32, L15.22, L15.32, L16.22, L16.32
VSS: A1.6, A1.7, A4.4, A11.13, A11.14, B11.7, B13.5, B13.6, B14.7, BB9.9, BG9.9, BR9.9, C4-1.6, C4-1.28, C4-2.7, C4-2.12, C4-3.4, C6.29, C7.14, C11.7, C12.7, C13.7, C14.12, C16.8, CC11.7, D6.1, D6.11, D7.14, D7.20, D9.16, D9.22, D10.16, D10.22, D13.3, D13.4, D13.5, D13.6, D15.8, D16.8, D18.1, D18.8, E4.1, E4.10, E4.30, E4.41, E4.50, E4.57, E4.59, E4.61, E4.62, E4.65, E4.66, E4.70, E4.72, E4.74, E4.81, E4.90, E4.110, E4.121, E4.130, E4.139, E4.150, E12.16, E12.53, E16.7, E17.7, E18.7, E18.12, F1.12, F1.31, F1.32, F2.5, F2.11, F2.14, F2.15, F4.7, F5.2, F5.7, F5.12, F6.16, F6.22, F7.14, F7.20, F9.16, F9.22, F10.16, F10.22, F13.14, F14.14, F15.14, F15.20, F16.7, F17.7, F18.7, G5.8, G5.9, G14.1, G14.15, G14.21, G14.31, G14.45, G14.61, G14.75, G14.91, G14.105, G17.7, G18.7, H1.11, H1.12, H1.13, H1.31, H2.11, H2.12, H2.13, H2.31, H9.12, H9.18, H10.12, H10.18, H11.7, H17.1, H17.10, J5.14, J5.20, J6.14, J6.20, J9.13, J9.15, J10.15, J11.15, J14.1, J14.15, J14.31, J14.45, J14.61, J14.75, J14.91, J14.94, J14.105, J17.1, J17.8, J17.10, J17.13, J17.14, J17.17, J17.18, K6.91, K6.101, K6.111, K6.117, K6.118, K10.1, K10.11, K10.21, K10.31, K10.41, K10.51, K10.61, K10.62, K10.63, K10.64, K10.65, K10.66, K10.67, K10.68, K10.69, K10.71, K10.81, K10.91, K10.101, K10.111, K13.15, K13.22, K13.40, K13.65, K13.67, K13.68, K13.69, K13.70, K13.71, K13.72, K13.73, K13.90, K13.94, L1.11, L1.12, L1.13, L1.31, L2.11, L2.12, L2.13, L2.31, L15.11, L15.12, L15.13, L15.31, L15.42, L16.11, L16.12, L16.13, L16.31, L16.42
